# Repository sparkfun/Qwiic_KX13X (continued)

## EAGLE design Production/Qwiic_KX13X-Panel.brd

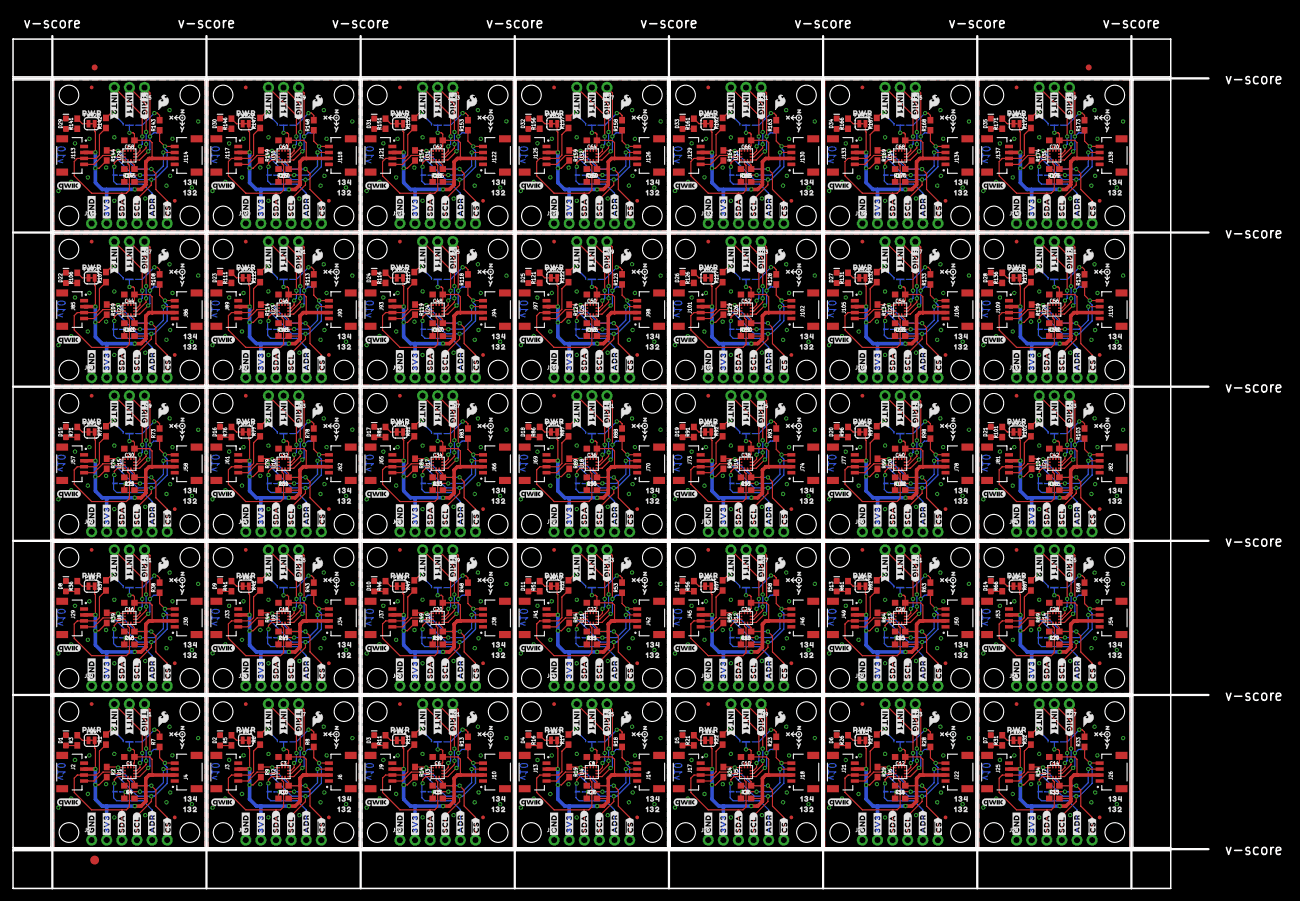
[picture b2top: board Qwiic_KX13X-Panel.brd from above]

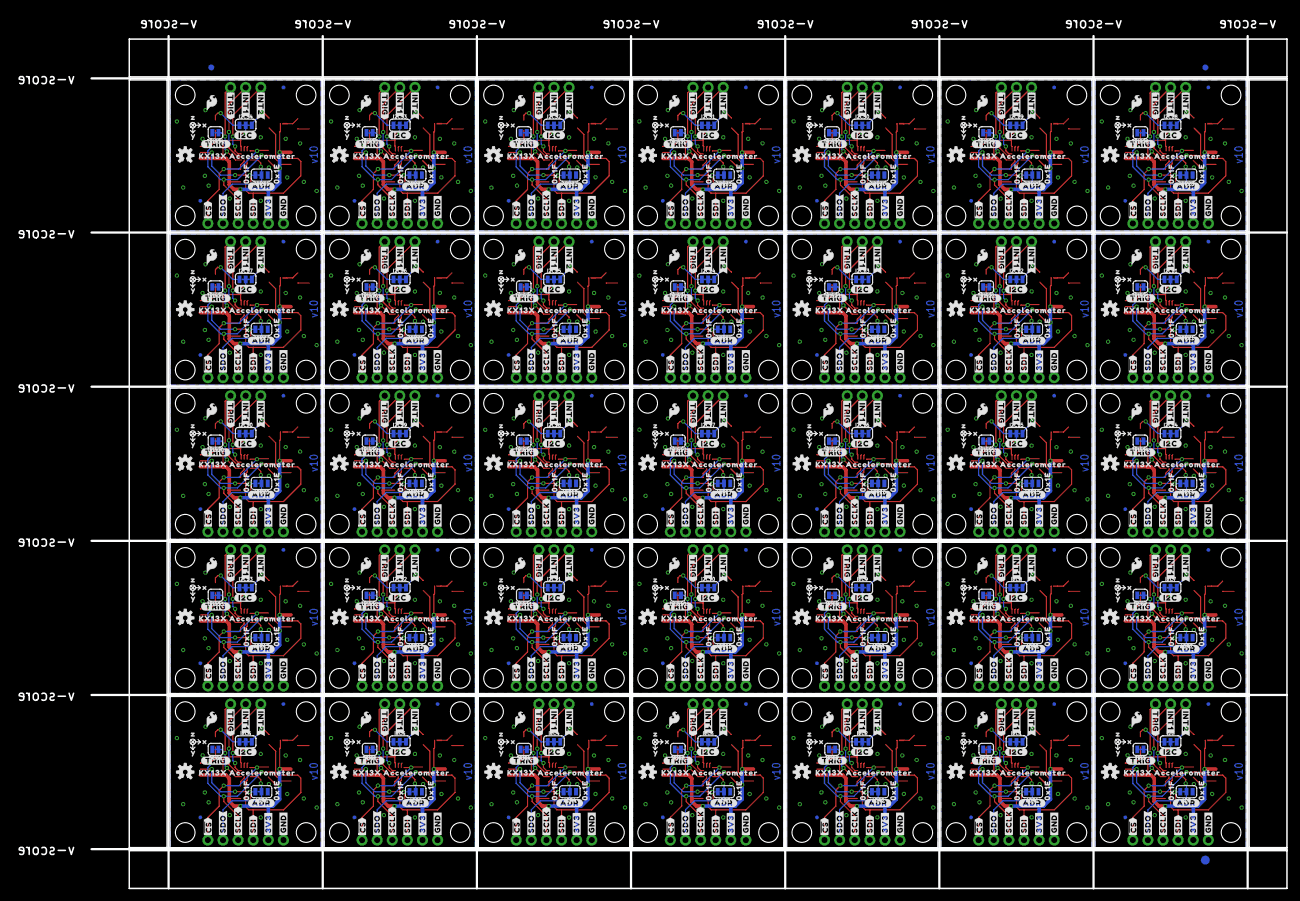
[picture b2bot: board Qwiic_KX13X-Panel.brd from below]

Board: 2 copper layers, 200.9 x 143.3 mm, 2176 parts (878 on the bottom side), 490 nets.

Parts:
ADR, ADR1, ADR2, ADR3, ADR4, ADR5, ADR6, ADR7, ADR8, ADR9, ADR10, ADR11, ADR12, ADR13, ADR14, ADR15, ADR16, ADR17, ADR18, ADR19, ADR20, ADR21, ADR22, ADR23, ADR24, ADR25, ADR26, ADR27, ADR28, ADR29, ADR30, ADR31, ADR32, ADR33, ADR34: JUMPER-SMT_3_1-NC_TRACE_SILK; SMT-JUMPER_3_1-NC_TRACE_SILK
C1, C2, C3, C4, C5, C6, C7, C8, C9, C10, C11, C12, C13, C14, C15, C16, C17, C18, C19, C20, C21, C22, C23, C24, C25, C26, C27, C28, C29, C30, C31, C32, C33, C34, C35, C36, C37, C38, C39, C40, C41, C42, C43, C44, C45, C46, C47, C48, C49, C50, C51, C52, C53, C54, C55, C56, C57, C58, C59, C60, C61, C62, C63, C64, C65, C66, C67, C68, C69, C70: 0.1uF; 0603
D1, D2, D3, D4, D5, D6, D7, D8, D9, D10, D11, D12, D13, D14, D15, D16, D17, D18, D19, D20, D21, D22, D23, D24, D25, D26, D27, D28, D29, D30, D31, D32, D33, D34, D35: RED; LED-0603
E$1, E$2, E$3, E$4: FIDUCIAL-1X2
E$5, E$6: FIDUCIAL-1.5X3
I2C, I2C1, I2C2, I2C3, I2C4, I2C5, I2C6, I2C7, I2C8, I2C9, I2C10, I2C11, I2C12, I2C13, I2C14, I2C15, I2C16, I2C17, I2C18, I2C19, I2C20, I2C21, I2C22, I2C23, I2C24, I2C25, I2C26, I2C27, I2C28, I2C29, I2C30, I2C31, I2C32, I2C33, I2C34: JUMPER-SMT_3_2-NC_TRACE_SILK; SMT-JUMPER_3_2-NC_TRACE_SILK
J1, J7, J11, J15, J19, J23, J27, J31, J35, J39, J43, J47, J51, J55, J59, J63, J67, J71, J75, J79, J83, J87, J91, J95, J99, J103, J107, J111, J115, J119, J123, J127, J131, J135, J139: 1X03_NO_SILK
J2, J3, J4, J6, J9, J10, J13, J14, J17, J18, J21, J22, J25, J26, J29, J30, J33, J34, J37, J38, J41, J42, J45, J46, J49, J50, J53, J54, J57, J58, J61, J62, J65, J66, J69, J70, J73, J74, J77, J78, J81, J82, J85, J86, J89, J90, J93, J94, J97, J98, J101, J102, J105, J106, J109, J110, J113, J114, J117, J118, J121, J122, J125, J126, J129, J130, J133, J134, J137, J138: QWIIC; JST04_1MM_RA
J5, J8, J12, J16, J20, J24, J28, J32, J36, J40, J44, J48, J52, J56, J60, J64, J68, J72, J76, J80, J84, J88, J92, J96, J100, J104, J108, J112, J116, J120, J124, J128, J132, J136, J140: 1X06_NO_SILK
JP1, JP2, JP5, JP6, JP11, JP12, JP13, JP14, JP19, JP20, JP21, JP22, JP27, JP28, JP29, JP30, JP35, JP36, JP37, JP38, JP43, JP44, JP45, JP46, JP51, JP52, JP53, JP54, JP59, JP60, JP61, JP62, JP67, JP68, JP69, JP70, JP75, JP76, JP77, JP78, JP83, JP84, JP85, JP86, JP91, JP92, JP93, JP94, JP99, JP100, JP101, JP102, JP107, JP108, JP109, JP110, JP115, JP116, JP117, JP118, JP123, JP124, JP125, JP126, JP131, JP132, JP133, JP134, JP139, JP140, JP141, JP142, JP147, JP148, JP149, JP150, JP155, JP156, JP157, JP158, JP163, JP164, JP165, JP166, JP171, JP172, JP173, JP174, JP179, JP180, JP181, JP182, JP187, JP188, JP189, JP190, JP195, JP196, JP197, JP198, JP203, JP204, JP205, JP206, JP211, JP212, JP213, JP214, JP219, JP220, JP221, JP222, JP227, JP228, JP229, JP230, JP235, JP236, JP237, JP238, JP243, JP244, JP245, JP246, JP251, JP252, JP253, JP254, JP259, JP260, JP261, JP262, JP267, JP268, JP269, JP270, JP275, JP276, JP277, JP278: FIDUCIALUFIDUCIAL; MICRO-FIDUCIAL
JP3, JP4, JP7, JP8, JP9, JP10, JP15, JP16, JP17, JP18, JP23, JP24, JP25, JP26, JP31, JP32, JP33, JP34, JP39, JP40, JP41, JP42, JP47, JP48, JP49, JP50, JP55, JP56, JP57, JP58, JP63, JP64, JP65, JP66, JP71, JP72, JP73, JP74, JP79, JP80, JP81, JP82, JP87, JP88, JP89, JP90, JP95, JP96, JP97, JP98, JP103, JP104, JP105, JP106, JP111, JP112, JP113, JP114, JP119, JP120, JP121, JP122, JP127, JP128, JP129, JP130, JP135, JP136, JP137, JP138, JP143, JP144, JP145, JP146, JP151, JP152, JP153, JP154, JP159, JP160, JP161, JP162, JP167, JP168, JP169, JP170, JP175, JP176, JP177, JP178, JP183, JP184, JP185, JP186, JP191, JP192, JP193, JP194, JP199, JP200, JP201, JP202, JP207, JP208, JP209, JP210, JP215, JP216, JP217, JP218, JP223, JP224, JP225, JP226, JP231, JP232, JP233, JP234, JP239, JP240, JP241, JP242, JP247, JP248, JP249, JP250, JP255, JP256, JP257, JP258, JP263, JP264, JP265, JP266, JP271, JP272, JP273, JP274, JP279, JP280: STAND-OFF
LOGO1, LOGO2, LOGO6, LOGO7, LOGO10, LOGO11, LOGO14, LOGO15, LOGO18, LOGO19, LOGO22, LOGO23, LOGO26, LOGO27, LOGO30, LOGO31, LOGO34, LOGO35, LOGO38, LOGO39, LOGO42, LOGO43, LOGO46, LOGO47, LOGO50, LOGO51, LOGO54, LOGO55, LOGO58, LOGO59, LOGO62, LOGO63, LOGO66, LOGO67, LOGO70, LOGO71, LOGO74, LOGO75, LOGO78, LOGO79, LOGO82, LOGO83, LOGO86, LOGO87, LOGO90, LOGO91, LOGO94, LOGO95, LOGO98, LOGO99, LOGO102, LOGO103, LOGO106, LOGO107, LOGO110, LOGO111, LOGO114, LOGO115, LOGO118, LOGO119, LOGO122, LOGO123, LOGO126, LOGO127, LOGO130, LOGO131, LOGO134, LOGO135, LOGO138, LOGO139: SFE_LOGO_FLAME.1_INCH; SFE_LOGO_FLAME_.1
LOGO3, LOGO8, LOGO12, LOGO16, LOGO20, LOGO24, LOGO28, LOGO32, LOGO36, LOGO40, LOGO44, LOGO48, LOGO52, LOGO56, LOGO60, LOGO64, LOGO68, LOGO72, LOGO76, LOGO80, LOGO84, LOGO88, LOGO92, LOGO96, LOGO100, LOGO104, LOGO108, LOGO112, LOGO116, LOGO120, LOGO124, LOGO128, LOGO132, LOGO136, LOGO140: QWIIC_LOGO_4MM; QWIIC_4MM
LOGO4, LOGO5, LOGO9, LOGO13, LOGO17, LOGO21, LOGO25, LOGO29, LOGO33, LOGO37, LOGO41, LOGO45, LOGO49, LOGO53, LOGO57, LOGO61, LOGO65, LOGO69, LOGO73, LOGO77, LOGO81, LOGO85, LOGO89, LOGO93, LOGO97, LOGO101, LOGO105, LOGO109, LOGO113, LOGO117, LOGO121, LOGO125, LOGO129, LOGO133, LOGO137: OSHW-LOGOS; OSHW-LOGO-S
PWR, PWR1, PWR2, PWR3, PWR4, PWR5, PWR6, PWR7, PWR8, PWR9, PWR10, PWR11, PWR12, PWR13, PWR14, PWR15, PWR16, PWR17, PWR18, PWR19, PWR20, PWR21, PWR22, PWR23, PWR24, PWR25, PWR26, PWR27, PWR28, PWR29, PWR30, PWR31, PWR32, PWR33, PWR34: JUMPER-SMT_2_NC_TRACE_SILK; SMT-JUMPER_2_NC_TRACE_SILK
R1, R2, R4, R6, R7, R8, R9, R10, R12, R13, R14, R15, R17, R18, R19, R20, R22, R23, R24, R25, R27, R28, R29, R30, R32, R33, R34, R35, R37, R38, R39, R40, R42, R43, R44, R45, R47, R48, R49, R50, R52, R53, R54, R55, R57, R58, R59, R60, R62, R63, R64, R65, R67, R68, R69, R70, R72, R73, R74, R75, R77, R78, R79, R80, R82, R83, R84, R85, R87, R88, R89, R90, R92, R93, R94, R95, R97, R98, R99, R100, R102, R103, R104, R105, R107, R108, R109, R110, R112, R113, R114, R115, R117, R118, R119, R120, R122, R123, R124, R125, R127, R128, R129, R130, R132, R133, R134, R135, R137, R138, R139, R140, R142, R143, R144, R145, R147, R148, R149, R150, R152, R153, R154, R155, R157, R158, R159, R160, R162, R163, R164, R165, R167, R168, R169, R170, R172, R173, R174, R175: 4.7k; 0603
R3, R5, R11, R16, R21, R26, R31, R36, R41, R46, R51, R56, R61, R66, R71, R76, R81, R86, R91, R96, R101, R106, R111, R116, R121, R126, R131, R136, R141, R146, R151, R156, R161, R166, R171: 1k; 0603
TRIG, TRIG1, TRIG2, TRIG3, TRIG4, TRIG5, TRIG6, TRIG7, TRIG8, TRIG9, TRIG10, TRIG11, TRIG12, TRIG13, TRIG14, TRIG15, TRIG16, TRIG17, TRIG18, TRIG19, TRIG20, TRIG21, TRIG22, TRIG23, TRIG24, TRIG25, TRIG26, TRIG27, TRIG28, TRIG29, TRIG30, TRIG31, TRIG32, TRIG33, TRIG34: JUMPER-SMT_2_NC_TRACE_SILK; SMT-JUMPER_2_NC_TRACE_SILK
U1, U2, U3, U4, U5, U6, U7, U8, U9, U10, U11, U12, U13, U14, U15, U16, U17, U18, U19, U20, U21, U22, U23, U24, U25, U26, U27, U28, U29, U30, U31, U32, U33, U34, U35: KX134; KX13X
U$1, U$28, U$52, U$61, U$85, U$94, U$118, U$127, U$151, U$160, U$184, U$193, U$217, U$226, U$250, U$259, U$283, U$292, U$316, U$325, U$349, U$358, U$382, U$391, U$415, U$424, U$448, U$457, U$481, U$490, U$514, U$523, U$547, U$556, U$580, U$589, U$613, U$622, U$646, U$655, U$679, U$688, U$712, U$721, U$745, U$754, U$778, U$787, U$811, U$820, U$844, U$853, U$877, U$886, U$910, U$919, U$943, U$952, U$976, U$985, U$1009, U$1018, U$1042, U$1051, U$1075, U$1084, U$1108, U$1117, U$1141, U$1150: X0
U$2, U$16, U$67, U$100, U$133, U$166, U$199, U$232, U$265, U$298, U$331, U$364, U$397, U$430, U$463, U$496, U$529, U$562, U$595, U$628, U$661, U$694, U$727, U$760, U$793, U$826, U$859, U$892, U$925, U$958, U$991, U$1024, U$1057, U$1090, U$1123: #SCL#0
U$3, U$35, U$68, U$101, U$134, U$167, U$200, U$233, U$266, U$299, U$332, U$365, U$398, U$431, U$464, U$497, U$530, U$563, U$596, U$629, U$662, U$695, U$728, U$761, U$794, U$827, U$860, U$893, U$926, U$959, U$992, U$1025, U$1058, U$1091, U$1124: #SDA#0
U$4, U$5, U$36, U$37, U$69, U$70, U$102, U$103, U$135, U$136, U$168, U$169, U$201, U$202, U$234, U$235, U$267, U$268, U$300, U$301, U$333, U$334, U$366, U$367, U$399, U$400, U$432, U$433, U$465, U$466, U$498, U$499, U$531, U$532, U$564, U$565, U$597, U$598, U$630, U$631, U$663, U$664, U$696, U$697, U$729, U$730, U$762, U$763, U$795, U$796, U$828, U$829, U$861, U$862, U$894, U$895, U$927, U$928, U$960, U$961, U$993, U$994, U$1026, U$1027, U$1059, U$1060, U$1092, U$1093, U$1125, U$1126: #3V3#0
U$6, U$7, U$38, U$39, U$71, U$72, U$104, U$105, U$137, U$138, U$170, U$171, U$203, U$204, U$236, U$237, U$269, U$270, U$302, U$303, U$335, U$336, U$368, U$369, U$401, U$402, U$434, U$435, U$467, U$468, U$500, U$501, U$533, U$534, U$566, U$567, U$599, U$600, U$632, U$633, U$665, U$666, U$698, U$699, U$731, U$732, U$764, U$765, U$797, U$798, U$830, U$831, U$863, U$864, U$896, U$897, U$929, U$930, U$962, U$963, U$995, U$996, U$1028, U$1029, U$1061, U$1062, U$1094, U$1095, U$1127, U$1128: #GND#0
U$8, U$9, U$40, U$41, U$73, U$74, U$106, U$107, U$139, U$140, U$172, U$173, U$205, U$206, U$238, U$239, U$271, U$272, U$304, U$305, U$337, U$338, U$370, U$371, U$403, U$404, U$436, U$437, U$469, U$470, U$502, U$503, U$535, U$536, U$568, U$569, U$601, U$602, U$634, U$635, U$667, U$668, U$700, U$701, U$733, U$734, U$766, U$767, U$799, U$800, U$832, U$833, U$865, U$866, U$898, U$899, U$931, U$932, U$964, U$965, U$997, U$998, U$1030, U$1031, U$1063, U$1064, U$1096, U$1097, U$1129, U$1130: ##CS##0
U$10, U$56, U$89, U$122, U$155, U$188, U$221, U$254, U$287, U$320, U$353, U$386, U$419, U$452, U$485, U$518, U$551, U$584, U$617, U$650, U$683, U$716, U$749, U$782, U$815, U$848, U$881, U$914, U$947, U$980, U$1013, U$1046, U$1079, U$1112, U$1145: #ADR#0
U$11, U$15, U$57, U$58, U$90, U$91, U$123, U$124, U$156, U$157, U$189, U$190, U$222, U$223, U$255, U$256, U$288, U$289, U$321, U$322, U$354, U$355, U$387, U$388, U$420, U$421, U$453, U$454, U$486, U$487, U$519, U$520, U$552, U$553, U$585, U$586, U$618, U$619, U$651, U$652, U$684, U$685, U$717, U$718, U$750, U$751, U$783, U$784, U$816, U$817, U$849, U$850, U$882, U$883, U$915, U$916, U$948, U$949, U$981, U$982, U$1014, U$1015, U$1047, U$1048, U$1080, U$1081, U$1113, U$1114, U$1146, U$1147: #TRIG#0
U$12, U$13, U$42, U$43, U$75, U$76, U$108, U$109, U$141, U$142, U$174, U$175, U$207, U$208, U$240, U$241, U$273, U$274, U$306, U$307, U$339, U$340, U$372, U$373, U$405, U$406, U$438, U$439, U$471, U$472, U$504, U$505, U$537, U$538, U$570, U$571, U$603, U$604, U$636, U$637, U$669, U$670, U$702, U$703, U$735, U$736, U$768, U$769, U$801, U$802, U$834, U$835, U$867, U$868, U$900, U$901, U$933, U$934, U$966, U$967, U$999, U$1000, U$1032, U$1033, U$1065, U$1066, U$1098, U$1099, U$1131, U$1132: #INT1#0
U$14, U$47, U$80, U$113, U$146, U$179, U$212, U$245, U$278, U$311, U$344, U$377, U$410, U$443, U$476, U$509, U$542, U$575, U$608, U$641, U$674, U$707, U$740, U$773, U$806, U$839, U$872, U$905, U$938, U$971, U$1004, U$1037, U$1070, U$1103, U$1136: 0X1E0
U$17, U$59, U$92, U$125, U$158, U$191, U$224, U$257, U$290, U$323, U$356, U$389, U$422, U$455, U$488, U$521, U$554, U$587, U$620, U$653, U$686, U$719, U$752, U$785, U$818, U$851, U$884, U$917, U$950, U$983, U$1016, U$1049, U$1082, U$1115, U$1148: #TRIG#2
U$18, U$19, U$44, U$45, U$77, U$78, U$110, U$111, U$143, U$144, U$176, U$177, U$209, U$210, U$242, U$243, U$275, U$276, U$308, U$309, U$341, U$342, U$374, U$375, U$407, U$408, U$440, U$441, U$473, U$474, U$506, U$507, U$539, U$540, U$572, U$573, U$605, U$606, U$638, U$639, U$671, U$672, U$704, U$705, U$737, U$738, U$770, U$771, U$803, U$804, U$836, U$837, U$869, U$870, U$902, U$903, U$935, U$936, U$968, U$969, U$1001, U$1002, U$1034, U$1035, U$1067, U$1068, U$1100, U$1101, U$1133, U$1134: #INT2#0
U$20, U$60, U$93, U$126, U$159, U$192, U$225, U$258, U$291, U$324, U$357, U$390, U$423, U$456, U$489, U$522, U$555, U$588, U$621, U$654, U$687, U$720, U$753, U$786, U$819, U$852, U$885, U$918, U$951, U$984, U$1017, U$1050, U$1083, U$1116, U$1149: #ADR#3
U$21, U$29, U$53, U$62, U$86, U$95, U$119, U$128, U$152, U$161, U$185, U$194, U$218, U$227, U$251, U$260, U$284, U$293, U$317, U$326, U$350, U$359, U$383, U$392, U$416, U$425, U$449, U$458, U$482, U$491, U$515, U$524, U$548, U$557, U$581, U$590, U$614, U$623, U$647, U$656, U$680, U$689, U$713, U$722, U$746, U$755, U$779, U$788, U$812, U$821, U$845, U$854, U$878, U$887, U$911, U$920, U$944, U$953, U$977, U$986, U$1010, U$1019, U$1043, U$1052, U$1076, U$1085, U$1109, U$1118, U$1142, U$1151: Y0
U$22, U$46, U$79, U$112, U$145, U$178, U$211, U$244, U$277, U$310, U$343, U$376, U$409, U$442, U$475, U$508, U$541, U$574, U$607, U$640, U$673, U$706, U$739, U$772, U$805, U$838, U$871, U$904, U$937, U$970, U$1003, U$1036, U$1069, U$1102, U$1135: #I2C#0
U$23, U$48, U$81, U$114, U$147, U$180, U$213, U$246, U$279, U$312, U$345, U$378, U$411, U$444, U$477, U$510, U$543, U$576, U$609, U$642, U$675, U$708, U$741, U$774, U$807, U$840, U$873, U$906, U$939, U$972, U$1005, U$1038, U$1071, U$1104, U$1137: 0X1F0
U$24, U$49, U$82, U$115, U$148, U$181, U$214, U$247, U$280, U$313, U$346, U$379, U$412, U$445, U$478, U$511, U$544, U$577, U$610, U$643, U$676, U$709, U$742, U$775, U$808, U$841, U$874, U$907, U$940, U$973, U$1006, U$1039, U$1072, U$1105, U$1138: #SDI#0
U$25, U$50, U$83, U$116, U$149, U$182, U$215, U$248, U$281, U$314, U$347, U$380, U$413, U$446, U$479, U$512, U$545, U$578, U$611, U$644, U$677, U$710, U$743, U$776, U$809, U$842, U$875, U$908, U$941, U$974, U$1007, U$1040, U$1073, U$1106, U$1139: #SCLK#0
U$26, U$51, U$84, U$117, U$150, U$183, U$216, U$249, U$282, U$315, U$348, U$381, U$414, U$447, U$480, U$513, U$546, U$579, U$612, U$645, U$678, U$711, U$744, U$777, U$810, U$843, U$876, U$909, U$942, U$975, U$1008, U$1041, U$1074, U$1107, U$1140: #SDO#0
U$27, U$66, U$99, U$132, U$165, U$198, U$231, U$264, U$297, U$330, U$363, U$396, U$429, U$462, U$495, U$528, U$561, U$594, U$627, U$660, U$693, U$726, U$759, U$792, U$825, U$858, U$891, U$924, U$957, U$990, U$1023, U$1056, U$1089, U$1122, U$1155: KX13X_ACCELEROMETER14
U$30, U$32, U$54, U$63, U$87, U$96, U$120, U$129, U$153, U$162, U$186, U$195, U$219, U$228, U$252, U$261, U$285, U$294, U$318, U$327, U$351, U$360, U$384, U$393, U$417, U$426, U$450, U$459, U$483, U$492, U$516, U$525, U$549, U$558, U$582, U$591, U$615, U$624, U$648, U$657, U$681, U$690, U$714, U$723, U$747, U$756, U$780, U$789, U$813, U$822, U$846, U$855, U$879, U$888, U$912, U$921, U$945, U$954, U$978, U$987, U$1011, U$1020, U$1044, U$1053, U$1077, U$1086, U$1110, U$1119, U$1143, U$1152: Z0
U$31, U$55, U$88, U$121, U$154, U$187, U$220, U$253, U$286, U$319, U$352, U$385, U$418, U$451, U$484, U$517, U$550, U$583, U$616, U$649, U$682, U$715, U$748, U$781, U$814, U$847, U$880, U$913, U$946, U$979, U$1012, U$1045, U$1078, U$1111, U$1144: PWR0
U$33, U$64, U$97, U$130, U$163, U$196, U$229, U$262, U$295, U$328, U$361, U$394, U$427, U$460, U$493, U$526, U$559, U$592, U$625, U$658, U$691, U$724, U$757, U$790, U$823, U$856, U$889, U$922, U$955, U$988, U$1021, U$1054, U$1087, U$1120, U$1153: 1320
U$34, U$65, U$98, U$131, U$164, U$197, U$230, U$263, U$296, U$329, U$362, U$395, U$428, U$461, U$494, U$527, U$560, U$593, U$626, U$659, U$692, U$725, U$758, U$791, U$824, U$857, U$890, U$923, U$956, U$989, U$1022, U$1055, U$1088, U$1121, U$1154: 1340

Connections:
3.3V: C1.1, C4.1, I2C.2, J2.2, J4.2, J5.2, PWR.2, R2.2, R4.2, U1.3, U1.7
3.3V1: C2.1, C3.1, I2C1.2, J3.2, J6.2, J8.2, PWR1.2, R9.2, R10.2, U2.3, U2.7
3.3V2: C5.1, C6.1, I2C2.2, J9.2, J10.2, J12.2, PWR2.2, R14.2, R15.2, U3.3, U3.7
3.3V3: C7.1, C8.1, I2C3.2, J13.2, J14.2, J16.2, PWR3.2, R19.2, R20.2, U4.3, U4.7
3.3V4: C9.1, C10.1, I2C4.2, J17.2, J18.2, J20.2, PWR4.2, R24.2, R25.2, U5.3, U5.7
3.3V5: C11.1, C12.1, I2C5.2, J21.2, J22.2, J24.2, PWR5.2, R29.2, R30.2, U6.3, U6.7
3.3V6: C13.1, C14.1, I2C6.2, J25.2, J26.2, J28.2, PWR6.2, R34.2, R35.2, U7.3, U7.7
3.3V7: C15.1, C16.1, I2C7.2, J29.2, J30.2, J32.2, PWR7.2, R39.2, R40.2, U8.3, U8.7
3.3V8: C17.1, C18.1, I2C8.2, J33.2, J34.2, J36.2, PWR8.2, R44.2, R45.2, U9.3, U9.7
3.3V9: C19.1, C20.1, I2C9.2, J37.2, J38.2, J40.2, PWR9.2, R49.2, R50.2, U10.3, U10.7
3.3V10: C21.1, C22.1, I2C10.2, J41.2, J42.2, J44.2, PWR10.2, R54.2, R55.2, U11.3, U11.7
3.3V11: C23.1, C24.1, I2C11.2, J45.2, J46.2, J48.2, PWR11.2, R59.2, R60.2, U12.3, U12.7
3.3V12: C25.1, C26.1, I2C12.2, J49.2, J50.2, J52.2, PWR12.2, R64.2, R65.2, U13.3, U13.7
3.3V13: C27.1, C28.1, I2C13.2, J53.2, J54.2, J56.2, PWR13.2, R69.2, R70.2, U14.3, U14.7
3.3V14: C29.1, C30.1, I2C14.2, J57.2, J58.2, J60.2, PWR14.2, R74.2, R75.2, U15.3, U15.7
3.3V15: C31.1, C32.1, I2C15.2, J61.2, J62.2, J64.2, PWR15.2, R79.2, R80.2, U16.3, U16.7
3.3V16: C33.1, C34.1, I2C16.2, J65.2, J66.2, J68.2, PWR16.2, R84.2, R85.2, U17.3, U17.7
3.3V17: C35.1, C36.1, I2C17.2, J69.2, J70.2, J72.2, PWR17.2, R89.2, R90.2, U18.3, U18.7
3.3V18: C37.1, C38.1, I2C18.2, J73.2, J74.2, J76.2, PWR18.2, R94.2, R95.2, U19.3, U19.7
3.3V19: C39.1, C40.1, I2C19.2, J77.2, J78.2, J80.2, PWR19.2, R99.2, R100.2, U20.3, U20.7
3.3V20: C41.1, C42.1, I2C20.2, J81.2, J82.2, J84.2, PWR20.2, R104.2, R105.2, U21.3, U21.7
3.3V21: C43.1, C44.1, I2C21.2, J85.2, J86.2, J88.2, PWR21.2, R109.2, R110.2, U22.3, U22.7
3.3V22: C45.1, C46.1, I2C22.2, J89.2, J90.2, J92.2, PWR22.2, R114.2, R115.2, U23.3, U23.7
3.3V23: C47.1, C48.1, I2C23.2, J93.2, J94.2, J96.2, PWR23.2, R119.2, R120.2, U24.3, U24.7
3.3V24: C49.1, C50.1, I2C24.2, J97.2, J98.2, J100.2, PWR24.2, R124.2, R125.2, U25.3, U25.7
3.3V25: C51.1, C52.1, I2C25.2, J101.2, J102.2, J104.2, PWR25.2, R129.2, R130.2, U26.3, U26.7
3.3V26: C53.1, C54.1, I2C26.2, J105.2, J106.2, J108.2, PWR26.2, R134.2, R135.2, U27.3, U27.7
3.3V27: C55.1, C56.1, I2C27.2, J109.2, J110.2, J112.2, PWR27.2, R139.2, R140.2, U28.3, U28.7
3.3V28: C57.1, C58.1, I2C28.2, J113.2, J114.2, J116.2, PWR28.2, R144.2, R145.2, U29.3, U29.7
3.3V29: C59.1, C60.1, I2C29.2, J117.2, J118.2, J120.2, PWR29.2, R149.2, R150.2, U30.3, U30.7
3.3V30: C61.1, C62.1, I2C30.2, J121.2, J122.2, J124.2, PWR30.2, R154.2, R155.2, U31.3, U31.7
3.3V31: C63.1, C64.1, I2C31.2, J125.2, J126.2, J128.2, PWR31.2, R159.2, R160.2, U32.3, U32.7
3.3V32: C65.1, C66.1, I2C32.2, J129.2, J130.2, J132.2, PWR32.2, R164.2, R165.2, U33.3, U33.7
3.3V33: C67.1, C68.1, I2C33.2, J133.2, J134.2, J136.2, PWR33.2, R169.2, R170.2, U34.3, U34.7
3.3V34: C69.1, C70.1, I2C34.2, J137.2, J138.2, J140.2, PWR34.2, R174.2, R175.2, U35.3, U35.7
!CS: J5.6, R2.1, U1.10
!CS1: J8.6, R9.1, U2.10
!CS2: J12.6, R14.1, U3.10
!CS3: J16.6, R19.1, U4.10
!CS4: J20.6, R24.1, U5.10
!CS5: J24.6, R29.1, U6.10
!CS6: J28.6, R34.1, U7.10
!CS7: J32.6, R39.1, U8.10
!CS8: J36.6, R44.1, U9.10
!CS9: J40.6, R49.1, U10.10
!CS10: J44.6, R54.1, U11.10
!CS11: J48.6, R59.1, U12.10
!CS12: J52.6, R64.1, U13.10
!CS13: J56.6, R69.1, U14.10
!CS14: J60.6, R74.1, U15.10
!CS15: J64.6, R79.1, U16.10
!CS16: J68.6, R84.1, U17.10
!CS17: J72.6, R89.1, U18.10
!CS18: J76.6, R94.1, U19.10
!CS19: J80.6, R99.1, U20.10
!CS20: J84.6, R104.1, U21.10
!CS21: J88.6, R109.1, U22.10
!CS22: J92.6, R114.1, U23.10
!CS23: J96.6, R119.1, U24.10
!CS24: J100.6, R124.1, U25.10
!CS25: J104.6, R129.1, U26.10
!CS26: J108.6, R134.1, U27.10
!CS27: J112.6, R139.1, U28.10
!CS28: J116.6, R144.1, U29.10
!CS29: J120.6, R149.1, U30.10
!CS30: J124.6, R154.1, U31.10
!CS31: J128.6, R159.1, U32.10
!CS32: J132.6, R164.1, U33.10
!CS33: J136.6, R169.1, U34.10
!CS34: J140.6, R174.1, U35.10
ADR/SDO: ADR.2, J5.5, U1.1
ADR/SDO1: ADR1.2, J8.5, U2.1
ADR/SDO2: ADR2.2, J12.5, U3.1
ADR/SDO3: ADR3.2, J16.5, U4.1
ADR/SDO4: ADR4.2, J20.5, U5.1
ADR/SDO5: ADR5.2, J24.5, U6.1
ADR/SDO6: ADR6.2, J28.5, U7.1
ADR/SDO7: ADR7.2, J32.5, U8.1
ADR/SDO8: ADR8.2, J36.5, U9.1
ADR/SDO9: ADR9.2, J40.5, U10.1
ADR/SDO10: ADR10.2, J44.5, U11.1
ADR/SDO11: ADR11.2, J48.5, U12.1
ADR/SDO12: ADR12.2, J52.5, U13.1
ADR/SDO13: ADR13.2, J56.5, U14.1
ADR/SDO14: ADR14.2, J60.5, U15.1
ADR/SDO15: ADR15.2, J64.5, U16.1
ADR/SDO16: ADR16.2, J68.5, U17.1
ADR/SDO17: ADR17.2, J72.5, U18.1
ADR/SDO18: ADR18.2, J76.5, U19.1
ADR/SDO19: ADR19.2, J80.5, U20.1
ADR/SDO20: ADR20.2, J84.5, U21.1
ADR/SDO21: ADR21.2, J88.5, U22.1
ADR/SDO22: ADR22.2, J92.5, U23.1
ADR/SDO23: ADR23.2, J96.5, U24.1
ADR/SDO24: ADR24.2, J100.5, U25.1
ADR/SDO25: ADR25.2, J104.5, U26.1
ADR/SDO26: ADR26.2, J108.5, U27.1
ADR/SDO27: ADR27.2, J112.5, U28.1
ADR/SDO28: ADR28.2, J116.5, U29.1
ADR/SDO29: ADR29.2, J120.5, U30.1
ADR/SDO30: ADR30.2, J124.5, U31.1
ADR/SDO31: ADR31.2, J128.5, U32.1
ADR/SDO32: ADR32.2, J132.5, U33.1
ADR/SDO33: ADR33.2, J136.5, U34.1
ADR/SDO34: ADR34.2, J140.5, U35.1
GND: ADR.1, C1.2, C4.2, D1.C, J2.1, J4.1, J5.1, TRIG.2, U1.8, U1.9
GND1: ADR1.1, C2.2, C3.2, D2.C, J3.1, J6.1, J8.1, TRIG1.2, U2.8, U2.9
GND2: ADR2.1, C5.2, C6.2, D3.C, J9.1, J10.1, J12.1, TRIG2.2, U3.8, U3.9
GND3: ADR3.1, C7.2, C8.2, D4.C, J13.1, J14.1, J16.1, TRIG3.2, U4.8, U4.9
GND4: ADR4.1, C9.2, C10.2, D5.C, J17.1, J18.1, J20.1, TRIG4.2, U5.8, U5.9
GND5: ADR5.1, C11.2, C12.2, D6.C, J21.1, J22.1, J24.1, TRIG5.2, U6.8, U6.9
GND6: ADR6.1, C13.2, C14.2, D7.C, J25.1, J26.1, J28.1, TRIG6.2, U7.8, U7.9
GND7: ADR7.1, C15.2, C16.2, D8.C, J29.1, J30.1, J32.1, TRIG7.2, U8.8, U8.9
GND8: ADR8.1, C17.2, C18.2, D9.C, J33.1, J34.1, J36.1, TRIG8.2, U9.8, U9.9
GND9: ADR9.1, C19.2, C20.2, D10.C, J37.1, J38.1, J40.1, TRIG9.2, U10.8, U10.9
GND10: ADR10.1, C21.2, C22.2, D11.C, J41.1, J42.1, J44.1, TRIG10.2, U11.8, U11.9
GND11: ADR11.1, C23.2, C24.2, D12.C, J45.1, J46.1, J48.1, TRIG11.2, U12.8, U12.9
GND12: ADR12.1, C25.2, C26.2, D13.C, J49.1, J50.1, J52.1, TRIG12.2, U13.8, U13.9
GND13: ADR13.1, C27.2, C28.2, D14.C, J53.1, J54.1, J56.1, TRIG13.2, U14.8, U14.9
GND14: ADR14.1, C29.2, C30.2, D15.C, J57.1, J58.1, J60.1, TRIG14.2, U15.8, U15.9
GND15: ADR15.1, C31.2, C32.2, D16.C, J61.1, J62.1, J64.1, TRIG15.2, U16.8, U16.9
GND16: ADR16.1, C33.2, C34.2, D17.C, J65.1, J66.1, J68.1, TRIG16.2, U17.8, U17.9
GND17: ADR17.1, C35.2, C36.2, D18.C, J69.1, J70.1, J72.1, TRIG17.2, U18.8, U18.9
GND18: ADR18.1, C37.2, C38.2, D19.C, J73.1, J74.1, J76.1, TRIG18.2, U19.8, U19.9
GND19: ADR19.1, C39.2, C40.2, D20.C, J77.1, J78.1, J80.1, TRIG19.2, U20.8, U20.9
GND20: ADR20.1, C41.2, C42.2, D21.C, J81.1, J82.1, J84.1, TRIG20.2, U21.8, U21.9
GND21: ADR21.1, C43.2, C44.2, D22.C, J85.1, J86.1, J88.1, TRIG21.2, U22.8, U22.9
GND22: ADR22.1, C45.2, C46.2, D23.C, J89.1, J90.1, J92.1, TRIG22.2, U23.8, U23.9
GND23: ADR23.1, C47.2, C48.2, D24.C, J93.1, J94.1, J96.1, TRIG23.2, U24.8, U24.9
GND24: ADR24.1, C49.2, C50.2, D25.C, J97.1, J98.1, J100.1, TRIG24.2, U25.8, U25.9
GND25: ADR25.1, C51.2, C52.2, D26.C, J101.1, J102.1, J104.1, TRIG25.2, U26.8, U26.9
GND26: ADR26.1, C53.2, C54.2, D27.C, J105.1, J106.1, J108.1, TRIG26.2, U27.8, U27.9
GND27: ADR27.1, C55.2, C56.2, D28.C, J109.1, J110.1, J112.1, TRIG27.2, U28.8, U28.9
GND28: ADR28.1, C57.2, C58.2, D29.C, J113.1, J114.1, J116.1, TRIG28.2, U29.8, U29.9
GND29: ADR29.1, C59.2, C60.2, D30.C, J117.1, J118.1, J120.1, TRIG29.2, U30.8, U30.9
GND30: ADR30.1, C61.2, C62.2, D31.C, J121.1, J122.1, J124.1, TRIG30.2, U31.8, U31.9
GND31: ADR31.1, C63.2, C64.2, D32.C, J125.1, J126.1, J128.1, TRIG31.2, U32.8, U32.9
GND32: ADR32.1, C65.2, C66.2, D33.C, J129.1, J130.1, J132.1, TRIG32.2, U33.8, U33.9
GND33: ADR33.1, C67.2, C68.2, D34.C, J133.1, J134.1, J136.1, TRIG33.2, U34.8, U34.9
GND34: ADR34.1, C69.2, C70.2, D35.C, J137.1, J138.1, J140.1, TRIG34.2, U35.8, U35.9
INT1: J1.2, U1.5
INT2: J1.3, U1.6
INT3: J7.2, U2.5
INT4: J7.3, U2.6
INT5: J11.2, U3.5
INT6: J11.3, U3.6
INT7: J15.2, U4.5
INT8: J15.3, U4.6
INT9: J19.2, U5.5
INT10: J19.3, U5.6
INT11: J23.2, U6.5
INT12: J23.3, U6.6
INT13: J27.2, U7.5
INT14: J27.3, U7.6
INT15: J31.2, U8.5
INT16: J31.3, U8.6
INT17: J35.2, U9.5
INT18: J35.3, U9.6
INT19: J39.2, U10.5
INT20: J39.3, U10.6
INT21: J43.2, U11.5
INT22: J43.3, U11.6
INT23: J47.2, U12.5
INT24: J47.3, U12.6
INT25: J51.2, U13.5
INT26: J51.3, U13.6
INT27: J55.2, U14.5
INT28: J55.3, U14.6
INT29: J59.2, U15.5
INT30: J59.3, U15.6
INT31: J63.2, U16.5
INT32: J63.3, U16.6
INT33: J67.2, U17.5
INT34: J67.3, U17.6
INT35: J71.2, U18.5
INT36: J71.3, U18.6
INT37: J75.2, U19.5
INT38: J75.3, U19.6
INT39: J79.2, U20.5
INT40: J79.3, U20.6
INT41: J83.2, U21.5
INT42: J83.3, U21.6
INT43: J87.2, U22.5
INT44: J87.3, U22.6
INT45: J91.2, U23.5
INT46: J91.3, U23.6
INT47: J95.2, U24.5
INT48: J95.3, U24.6
INT49: J99.2, U25.5
INT50: J99.3, U25.6
INT51: J103.2, U26.5
INT52: J103.3, U26.6
INT53: J107.2, U27.5
INT54: J107.3, U27.6
INT55: J111.2, U28.5
INT56: J111.3, U28.6
INT57: J115.2, U29.5
INT58: J115.3, U29.6
INT59: J119.2, U30.5
INT60: J119.3, U30.6
INT61: J123.2, U31.5
INT62: J123.3, U31.6
INT63: J127.2, U32.5
INT64: J127.3, U32.6
INT65: J131.2, U33.5
INT66: J131.3, U33.6
INT67: J135.2, U34.5
INT68: J135.3, U34.6
INT69: J139.2, U35.5
INT70: J139.3, U35.6
unnamed: PWR.1, R3.2
unnamed: I2C.3, R1.2
unnamed: D1.A, R3.1
unnamed: I2C.1, R7.2
unnamed: ADR.3, R4.1
unnamed: D2.A, R5.1
unnamed: PWR1.1, R5.2
unnamed: I2C1.3, R6.2
unnamed: I2C1.1, R8.2
unnamed: ADR1.3, R10.1
unnamed: D3.A, R11.1
unnamed: PWR2.1, R11.2
unnamed: I2C2.3, R12.2
unnamed: I2C2.1, R13.2
unnamed: ADR2.3, R15.1
unnamed: D4.A, R16.1
unnamed: PWR3.1, R16.2
unnamed: I2C3.3, R17.2
unnamed: I2C3.1, R18.2
unnamed: ADR3.3, R20.1
unnamed: D5.A, R21.1
unnamed: PWR4.1, R21.2
unnamed: I2C4.3, R22.2
unnamed: I2C4.1, R23.2
unnamed: ADR4.3, R25.1
unnamed: D6.A, R26.1
unnamed: PWR5.1, R26.2
unnamed: I2C5.3, R27.2
unnamed: I2C5.1, R28.2
unnamed: ADR5.3, R30.1
unnamed: D7.A, R31.1
unnamed: PWR6.1, R31.2
unnamed: I2C6.3, R32.2
unnamed: I2C6.1, R33.2
unnamed: ADR6.3, R35.1
unnamed: D8.A, R36.1
unnamed: PWR7.1, R36.2
unnamed: I2C7.3, R37.2
unnamed: I2C7.1, R38.2
unnamed: ADR7.3, R40.1
unnamed: D9.A, R41.1
unnamed: PWR8.1, R41.2
unnamed: I2C8.3, R42.2
unnamed: I2C8.1, R43.2
unnamed: ADR8.3, R45.1
unnamed: D10.A, R46.1
unnamed: PWR9.1, R46.2
unnamed: I2C9.3, R47.2
unnamed: I2C9.1, R48.2
unnamed: ADR9.3, R50.1
unnamed: D11.A, R51.1
unnamed: PWR10.1, R51.2
unnamed: I2C10.3, R52.2
unnamed: I2C10.1, R53.2
unnamed: ADR10.3, R55.1
unnamed: D12.A, R56.1
unnamed: PWR11.1, R56.2
unnamed: I2C11.3, R57.2
unnamed: I2C11.1, R58.2
unnamed: ADR11.3, R60.1
unnamed: D13.A, R61.1
unnamed: PWR12.1, R61.2
unnamed: I2C12.3, R62.2
unnamed: I2C12.1, R63.2
unnamed: ADR12.3, R65.1
unnamed: D14.A, R66.1
unnamed: PWR13.1, R66.2
unnamed: I2C13.3, R67.2
unnamed: I2C13.1, R68.2
unnamed: ADR13.3, R70.1
unnamed: D15.A, R71.1
unnamed: PWR14.1, R71.2
unnamed: I2C14.3, R72.2
unnamed: I2C14.1, R73.2
unnamed: ADR14.3, R75.1
unnamed: D16.A, R76.1
unnamed: PWR15.1, R76.2
unnamed: I2C15.3, R77.2
unnamed: I2C15.1, R78.2
unnamed: ADR15.3, R80.1
unnamed: D17.A, R81.1
unnamed: PWR16.1, R81.2
unnamed: I2C16.3, R82.2
unnamed: I2C16.1, R83.2
unnamed: ADR16.3, R85.1
unnamed: D18.A, R86.1
unnamed: PWR17.1, R86.2
unnamed: I2C17.3, R87.2
unnamed: I2C17.1, R88.2
unnamed: ADR17.3, R90.1
unnamed: D19.A, R91.1
unnamed: PWR18.1, R91.2
unnamed: I2C18.3, R92.2
unnamed: I2C18.1, R93.2
unnamed: ADR18.3, R95.1
unnamed: D20.A, R96.1
unnamed: PWR19.1, R96.2
unnamed: I2C19.3, R97.2
unnamed: I2C19.1, R98.2
unnamed: ADR19.3, R100.1
unnamed: D21.A, R101.1
unnamed: PWR20.1, R101.2
unnamed: I2C20.3, R102.2
unnamed: I2C20.1, R103.2
unnamed: ADR20.3, R105.1
unnamed: D22.A, R106.1
unnamed: PWR21.1, R106.2
unnamed: I2C21.3, R107.2
unnamed: I2C21.1, R108.2
unnamed: ADR21.3, R110.1
unnamed: D23.A, R111.1
unnamed: PWR22.1, R111.2
unnamed: I2C22.3, R112.2
unnamed: I2C22.1, R113.2
unnamed: ADR22.3, R115.1
unnamed: D24.A, R116.1
unnamed: PWR23.1, R116.2
unnamed: I2C23.3, R117.2
unnamed: I2C23.1, R118.2
unnamed: ADR23.3, R120.1
unnamed: D25.A, R121.1
unnamed: PWR24.1, R121.2
unnamed: I2C24.3, R122.2
unnamed: I2C24.1, R123.2
unnamed: ADR24.3, R125.1
unnamed: D26.A, R126.1
unnamed: PWR25.1, R126.2
unnamed: I2C25.3, R127.2
unnamed: I2C25.1, R128.2
unnamed: ADR25.3, R130.1
unnamed: D27.A, R131.1
unnamed: PWR26.1, R131.2
unnamed: I2C26.3, R132.2
unnamed: I2C26.1, R133.2
unnamed: ADR26.3, R135.1
unnamed: D28.A, R136.1
unnamed: PWR27.1, R136.2
unnamed: I2C27.3, R137.2
unnamed: I2C27.1, R138.2
unnamed: ADR27.3, R140.1
unnamed: D29.A, R141.1
unnamed: PWR28.1, R141.2
unnamed: I2C28.3, R142.2
unnamed: I2C28.1, R143.2
unnamed: ADR28.3, R145.1
unnamed: D30.A, R146.1
unnamed: PWR29.1, R146.2
unnamed: I2C29.3, R147.2
unnamed: I2C29.1, R148.2
unnamed: ADR29.3, R150.1
unnamed: D31.A, R151.1
unnamed: PWR30.1, R151.2
unnamed: I2C30.3, R152.2
unnamed: I2C30.1, R153.2
unnamed: ADR30.3, R155.1
unnamed: D32.A, R156.1
unnamed: PWR31.1, R156.2
unnamed: I2C31.3, R157.2
unnamed: I2C31.1, R158.2
unnamed: ADR31.3, R160.1
unnamed: D33.A, R161.1
unnamed: PWR32.1, R161.2
unnamed: I2C32.3, R162.2
unnamed: I2C32.1, R163.2
unnamed: ADR32.3, R165.1
unnamed: D34.A, R166.1
unnamed: PWR33.1, R166.2
unnamed: I2C33.3, R167.2
unnamed: I2C33.1, R168.2
unnamed: ADR33.3, R170.1
unnamed: D35.A, R171.1
unnamed: PWR34.1, R171.2
unnamed: I2C34.3, R172.2
unnamed: I2C34.1, R173.2
unnamed: ADR34.3, R175.1
SCL/SCLK: J2.4, J4.4, J5.4, R7.1, U1.12
SCL/SCLK1: J3.4, J6.4, J8.4, R8.1, U2.12
SCL/SCLK2: J9.4, J10.4, J12.4, R13.1, U3.12
SCL/SCLK3: J13.4, J14.4, J16.4, R18.1, U4.12
SCL/SCLK4: J17.4, J18.4, J20.4, R23.1, U5.12
SCL/SCLK5: J21.4, J22.4, J24.4, R28.1, U6.12
SCL/SCLK6: J25.4, J26.4, J28.4, R33.1, U7.12
SCL/SCLK7: J29.4, J30.4, J32.4, R38.1, U8.12
SCL/SCLK8: J33.4, J34.4, J36.4, R43.1, U9.12
SCL/SCLK9: J37.4, J38.4, J40.4, R48.1, U10.12
SCL/SCLK10: J41.4, J42.4, J44.4, R53.1, U11.12
SCL/SCLK11: J45.4, J46.4, J48.4, R58.1, U12.12
SCL/SCLK12: J49.4, J50.4, J52.4, R63.1, U13.12
SCL/SCLK13: J53.4, J54.4, J56.4, R68.1, U14.12
SCL/SCLK14: J57.4, J58.4, J60.4, R73.1, U15.12
SCL/SCLK15: J61.4, J62.4, J64.4, R78.1, U16.12
SCL/SCLK16: J65.4, J66.4, J68.4, R83.1, U17.12
SCL/SCLK17: J69.4, J70.4, J72.4, R88.1, U18.12
SCL/SCLK18: J73.4, J74.4, J76.4, R93.1, U19.12
SCL/SCLK19: J77.4, J78.4, J80.4, R98.1, U20.12
SCL/SCLK20: J81.4, J82.4, J84.4, R103.1, U21.12
SCL/SCLK21: J85.4, J86.4, J88.4, R108.1, U22.12
SCL/SCLK22: J89.4, J90.4, J92.4, R113.1, U23.12
SCL/SCLK23: J93.4, J94.4, J96.4, R118.1, U24.12
SCL/SCLK24: J97.4, J98.4, J100.4, R123.1, U25.12
SCL/SCLK25: J101.4, J102.4, J104.4, R128.1, U26.12
SCL/SCLK26: J105.4, J106.4, J108.4, R133.1, U27.12
SCL/SCLK27: J109.4, J110.4, J112.4, R138.1, U28.12
SCL/SCLK28: J113.4, J114.4, J116.4, R143.1, U29.12
SCL/SCLK29: J117.4, J118.4, J120.4, R148.1, U30.12
SCL/SCLK30: J121.4, J122.4, J124.4, R153.1, U31.12
SCL/SCLK31: J125.4, J126.4, J128.4, R158.1, U32.12
SCL/SCLK32: J129.4, J130.4, J132.4, R163.1, U33.12
SCL/SCLK33: J133.4, J134.4, J136.4, R168.1, U34.12
SCL/SCLK34: J137.4, J138.4, J140.4, R173.1, U35.12
SDA/SDI: J2.3, J4.3, J5.3, R1.1, U1.2
SDA/SDI1: J3.3, J6.3, J8.3, R6.1, U2.2
SDA/SDI2: J9.3, J10.3, J12.3, R12.1, U3.2
SDA/SDI3: J13.3, J14.3, J16.3, R17.1, U4.2
SDA/SDI4: J17.3, J18.3, J20.3, R22.1, U5.2
SDA/SDI5: J21.3, J22.3, J24.3, R27.1, U6.2
SDA/SDI6: J25.3, J26.3, J28.3, R32.1, U7.2
SDA/SDI7: J29.3, J30.3, J32.3, R37.1, U8.2
SDA/SDI8: J33.3, J34.3, J36.3, R42.1, U9.2
SDA/SDI9: J37.3, J38.3, J40.3, R47.1, U10.2
SDA/SDI10: J41.3, J42.3, J44.3, R52.1, U11.2
SDA/SDI11: J45.3, J46.3, J48.3, R57.1, U12.2
SDA/SDI12: J49.3, J50.3, J52.3, R62.1, U13.2
SDA/SDI13: J53.3, J54.3, J56.3, R67.1, U14.2
SDA/SDI14: J57.3, J58.3, J60.3, R72.1, U15.2
SDA/SDI15: J61.3, J62.3, J64.3, R77.1, U16.2
SDA/SDI16: J65.3, J66.3, J68.3, R82.1, U17.2
SDA/SDI17: J69.3, J70.3, J72.3, R87.1, U18.2
SDA/SDI18: J73.3, J74.3, J76.3, R92.1, U19.2
SDA/SDI19: J77.3, J78.3, J80.3, R97.1, U20.2
SDA/SDI20: J81.3, J82.3, J84.3, R102.1, U21.2
SDA/SDI21: J85.3, J86.3, J88.3, R107.1, U22.2
SDA/SDI22: J89.3, J90.3, J92.3, R112.1, U23.2
SDA/SDI23: J93.3, J94.3, J96.3, R117.1, U24.2
SDA/SDI24: J97.3, J98.3, J100.3, R122.1, U25.2
SDA/SDI25: J101.3, J102.3, J104.3, R127.1, U26.2
SDA/SDI26: J105.3, J106.3, J108.3, R132.1, U27.2
SDA/SDI27: J109.3, J110.3, J112.3, R137.1, U28.2
SDA/SDI28: J113.3, J114.3, J116.3, R142.1, U29.2
SDA/SDI29: J117.3, J118.3, J120.3, R147.1, U30.2
SDA/SDI30: J121.3, J122.3, J124.3, R152.1, U31.2
SDA/SDI31: J125.3, J126.3, J128.3, R157.1, U32.2
SDA/SDI32: J129.3, J130.3, J132.3, R162.1, U33.2
SDA/SDI33: J133.3, J134.3, J136.3, R167.1, U34.2
SDA/SDI34: J137.3, J138.3, J140.3, R172.1, U35.2
TRIG: J1.1, TRIG.1, U1.4
TRIG1: J7.1, TRIG1.1, U2.4
TRIG2: J11.1, TRIG2.1, U3.4
TRIG3: J15.1, TRIG3.1, U4.4
TRIG4: J19.1, TRIG4.1, U5.4
TRIG5: J23.1, TRIG5.1, U6.4
TRIG6: J27.1, TRIG6.1, U7.4
TRIG7: J31.1, TRIG7.1, U8.4
TRIG8: J35.1, TRIG8.1, U9.4
TRIG9: J39.1, TRIG9.1, U10.4
TRIG10: J43.1, TRIG10.1, U11.4
TRIG11: J47.1, TRIG11.1, U12.4
TRIG12: J51.1, TRIG12.1, U13.4
TRIG13: J55.1, TRIG13.1, U14.4
TRIG14: J59.1, TRIG14.1, U15.4
TRIG15: J63.1, TRIG15.1, U16.4
TRIG16: J67.1, TRIG16.1, U17.4
TRIG17: J71.1, TRIG17.1, U18.4
TRIG18: J75.1, TRIG18.1, U19.4
TRIG19: J79.1, TRIG19.1, U20.4
TRIG20: J83.1, TRIG20.1, U21.4
TRIG21: J87.1, TRIG21.1, U22.4
TRIG22: J91.1, TRIG22.1, U23.4
TRIG23: J95.1, TRIG23.1, U24.4
TRIG24: J99.1, TRIG24.1, U25.4
TRIG25: J103.1, TRIG25.1, U26.4
TRIG26: J107.1, TRIG26.1, U27.4
TRIG27: J111.1, TRIG27.1, U28.4
TRIG28: J115.1, TRIG28.1, U29.4
TRIG29: J119.1, TRIG29.1, U30.4
TRIG30: J123.1, TRIG30.1, U31.4
TRIG31: J127.1, TRIG31.1, U32.4
TRIG32: J131.1, TRIG32.1, U33.4
TRIG33: J135.1, TRIG33.1, U34.4
TRIG34: J139.1, TRIG34.1, U35.4

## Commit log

2020-11-09 adding axes
2020-11-11 Post review/checklist changes
2021-01-14 adding 132/134 checkboxes
2021-01-18 updating version number and orientation for review
2021-01-19 post design review, computer transfer
2021-01-20 post checklist changes
2021-01-21 adding panels
2021-03-16 Adds documentation and gitignore
2021-03-24 Repanelizes design after fixing silk
    * There is a single PCB but there are jumpers with paste to indicate version. The paste layers have been placed into their own files with the production folder so that production can order the correc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
2021-05-04 Create README.md
    Initial README commit.
2026-03-17 initial work on porting to HUG to dinoland - works locally
2026-03-17 added hardware assembly
2026-03-17 fixing images as part of port
2026-03-17 more cleanup
2026-03-20 moved docs to gh pages and docusaurus - yay
2026-03-20 fix issue with secrets
